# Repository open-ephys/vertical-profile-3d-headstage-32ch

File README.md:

# vertical-profile-3d-headstage-32ch
Design files of a 32 channels headstage with 3D orientation using the same Intan's form factor.

## Licensing

The designs, documentation, and photos available in this repository are free: you can redistribute it and/or modify it under the terms of the used license.
Check the file named LICENSE.

<br />This work is licensed under a <a rel="license" href="http://creativecommons.org/licenses/by-nc-sa/3.0/igo/">Creative Commons Attribution-NonCommercial-ShareAlike 3.0 IGO License</a>.

[1]: https://docs.google.com/spreadsheets/d/1aobmmEzBDethzIlrm1eg0eYkBqlyX3s9WbA9KgRwVQI/edit?usp=sharing

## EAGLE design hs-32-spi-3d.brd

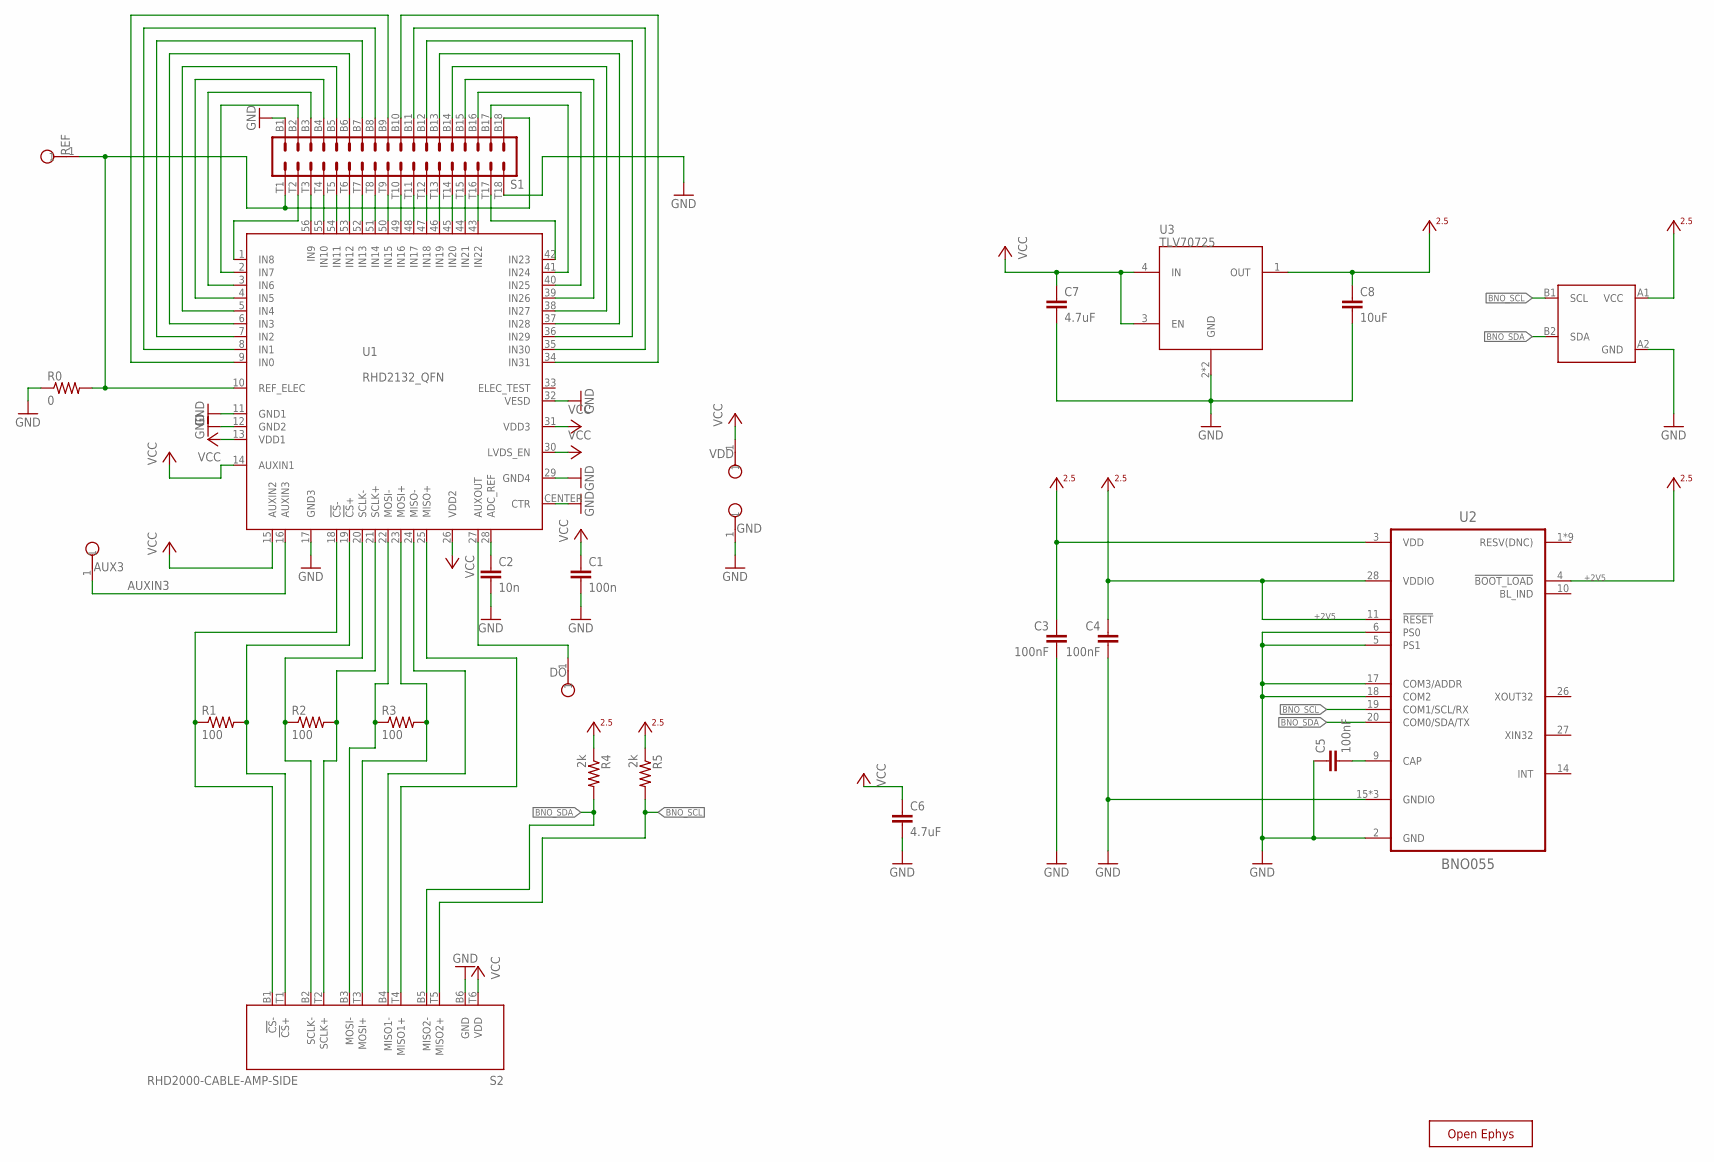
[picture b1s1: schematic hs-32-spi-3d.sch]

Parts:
AUX3: TESTPOINT_SMALL
C1: 100n; 0402
C2: 10n; 0402
C3, C4: 100nF; 0402T
C5: 100nF; 0201T
C6: 4.7uF; 0402
C7: 4.7uF; 0402T; PARTNO CL05A105KO5NNNC
C8: 10uF; 0402T; PARTNO CL05A106MQ5NUNC
DO: TESTPOINT_SMALL
GND: TESTPOINT_SMALL
R0: 0; 0402
R1, R2, R3: 100; 0402
R4, R5: 2k; 0201T
REF: TESTPOINT_SMALL
S1: OMNETICS_A79025
S2: RHD2000-CABLE-AMP-SIDE; OMNETICS_PZN-12-AA
U1: RHD2132_QFN; QFN56_8_X_8_LARGE
U2: BNO055; LGA-28-3.8X5.2
U3: TLV70725; X2SON
U4: 24CW640T-I/CS0668; 4-BALL_WAFFER_0.4MMX0.4MM
VDD: TESTPOINT_SMALL
X: OE-LOGO_3.5X2.5; OE-LOGO-3.5X2.5

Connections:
+2V5: C3.1, C4.1, C8.1, R4.1, R5.1, U2.3 (VDD), U2.4 (!BOOT_LOAD), U2.11 (!RESET), U2.28 (VDDIO), U3.1 (OUT), U4.A1 (VCC)
AUXIN3: AUX3.1, U1.16 (AUXIN3)
BNO_SCL: R5.2, S2.T5 (MISO2+), U2.19 (COM1/SCL/RX), U4.B1 (SCL)
BNO_SDA: R4.2, S2.B5 (MISO2-), U2.20 (COM0/SDA/TX), U4.B2 (SDA)
GND: C1.2, C2.2, C3.2, C4.2, C5.1, C6.2, C7.2, C8.2, GND.1, R0.1, S1.B1, S1.T18, S2.B6 (GND), U1.11 (GND1), U1.12 (GND2), U1.17 (GND3), U1.29 (GND4), U1.32 (VESD), U1.CENTER (CTR), U2.2 (GND), U2.5 (PS1), U2.6 (PS0), U2.15 (GNDIO), U2.16 (GNDIO), U2.17 (COM3/ADDR), U2.18 (COM2), U2.25 (GNDIO), U3.2 (GND), U3.PAD (GND), U4.A2 (GND)
unnamed: R0.2, REF.1, S1.B18, S1.T1, U1.10 (REF_ELEC)
unnamed: S1.B3, U1.3 (IN6)
unnamed: S1.B2, U1.2 (IN7)
unnamed: S1.B4, U1.4 (IN5)
unnamed: S1.B5, U1.5 (IN4)
unnamed: S1.B6, U1.6 (IN3)
unnamed: S1.B7, U1.7 (IN2)
unnamed: S1.B8, U1.8 (IN1)
unnamed: S1.B9, U1.9 (IN0)
unnamed: S1.B10, U1.34 (IN31)
unnamed: R1.1, S2.B1 (!CS!-), U1.18 (!CS!-)
unnamed: S1.B17, U1.41 (IN24)
unnamed: S1.B16, U1.40 (IN25)
unnamed: S1.B15, U1.39 (IN26)
unnamed: S1.B14, U1.38 (IN27)
unnamed: S1.B13, U1.37 (IN28)
unnamed: S1.B12, U1.36 (IN29)
unnamed: S1.B11, U1.35 (IN30)
unnamed: S1.T9, U1.50 (IN15)
unnamed: S1.T8, U1.51 (IN14)
unnamed: S1.T7, U1.52 (IN13)
unnamed: S1.T3, U1.56 (IN9)
unnamed: S1.T4, U1.55 (IN10)
unnamed: S1.T5, U1.54 (IN11)
unnamed: S1.T6, U1.53 (IN12)
unnamed: S1.T10, U1.49 (IN16)
unnamed: S1.T11, U1.48 (IN17)
unnamed: S1.T12, U1.47 (IN18)
unnamed: S1.T13, U1.46 (IN19)
unnamed: S1.T14, U1.45 (IN20)
unnamed: S1.T15, U1.44 (IN21)
unnamed: S1.T16, U1.43 (IN22)
unnamed: S1.T2, U1.1 (IN8)
unnamed: S1.T17, U1.42 (IN23)
unnamed: R1.2, S2.T1 (!CS!+), U1.19 (!CS!+)
unnamed: R2.1, S2.B2 (SCLK-), U1.20 (SCLK-)
unnamed: R2.2, S2.T2 (SCLK+), U1.21 (SCLK+)
unnamed: R3.1, S2.B3 (MOSI-), U1.22 (MOSI-)
unnamed: R3.2, S2.T3 (MOSI+), U1.23 (MOSI+)
unnamed: S2.B4 (MISO1-), U1.24 (MISO-)
unnamed: S2.T4 (MISO1+), U1.25 (MISO+)
unnamed: C2.1, U1.28 (ADC_REF)
unnamed: DO.1, U1.27 (AUXOUT)
unnamed: C5.2, U2.9 (CAP)
VCC: C1.1, C6.1, C7.1, S2.T6 (VDD), U1.13 (VDD1), U1.14 (AUXIN1), U1.15 (AUXIN2), U1.26 (VDD2), U1.30 (LVDS_EN), U1.31 (VDD3), U3.3 (EN), U3.4 (IN), VDD.1

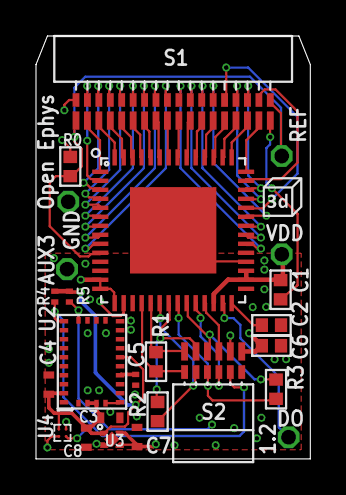
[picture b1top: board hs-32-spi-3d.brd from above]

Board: 4 copper layers, 15.2 x 23.5 mm, 26 parts (1 on the bottom side), 50 nets.

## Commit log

2023-10-06 Created README.md.
2023-10-07 Added PCB design files.
2023-10-07 Added first production files.
2023-10-07 Increased minimum drill to 0.25 mm.
    Also created a pad for the AUXIN3.
2023-10-07 Added components centroids.
2023-10-07 Corrected C6 and C7 values to 4.7uF.
2024-10-17 Added 3d logo.
2024-10-17 Updated production files.
2024-10-17 Added license.
2025-02-13 Minor corrections.
2025-02-13 Added .gitignore.
2025-02-18 Added EEPROM.
2025-03-04 Cleaned DRC.
2025-03-04 Minor details regarding capacitors' nomenclature.
